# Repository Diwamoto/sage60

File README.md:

# Sage60

60% の分割キーボード。左右とも nRF52840（MX 版は XIAO nRF52840）で、左右間・PC とは BLE で無線接続する。右手の親指側にトラックボール（PMW3610）。
スイッチは MX / Kailh Choc v2（同じ PCB）と、東プレ（静電容量）版がある。

**[ギャラリーサイト](https://diwamoto.github.io/sage60/)**: 3D モデルと構造の解説（`case/site/`）

## ディレクトリ

| パス | 中身 |
| --- | --- |
| `pcb/mx/`, `pcb/ec/` | KiCad の基板・回路図（`pcb/README.md`） |
| `case/` | ケースを KiCad から作るスクリプト（Python + Fusion）。ガスケットマウント、磁石固定、MX とロープロファイル（`case/README.md`） |
| `case/trackball/` | トラックボールケースの改造スクリプトと取得手順（ケース本体は fork） |
| `firmware/zmk/` | ZMK の設定（shield `sage60` = MX、`sage60_ec` = 東プレ）。`build.sh` でローカルビルド、GitHub Actions でもビルド |
| `production/` | 発注・印刷に使う出力物 |
| `docs/` | 配列（`kle.json`）、配線図（`sage60_wiring.drawio`）、画像 |

`production/` の中身:

| パス | 用途 |
| --- | --- |
| `case_cnc/` | ケース上下の STEP（JLCCNC） |
| `case_print/` | ケース上下・MCU カバー・シムの 3MF / STL（3D プリント） |
| `plate/` | プレートの DXF（外形の元データ。ケース生成もここから読む）/ STEP（金属）、3MF（プリント） |
| `mcu_cover/` | MCU カバーの DXF（ウォルナット） |

## ファームウェア

ZMK。東プレ版は nRF52840 の ADC で静電容量を読んでキー入力を判定する（判定方法は[こちら](https://nogikes.booth.pm/items/2373281)、[こちら](https://booth.pm/ja/items/2232932)を参考）。

## ライセンス

MIT（`LICENSE`）。PMW3610 センサー基板とトラックボールケースは GPL-3.0 なので [Diwamoto/roBa の `sage60` ブランチ](https://github.com/Diwamoto/roBa/tree/sage60) に分けている。

## 参考
* zmk の設定: [tako-config](https://github.com/ssbb/tako-config)
* 基板: [tako](https://github.com/ssbb/tako)
* センサー基板・トラックボールケース: [roBa](https://github.com/kumamuk-git/roBa)（ケースの元は Keyball Trackball Case by kepeo）

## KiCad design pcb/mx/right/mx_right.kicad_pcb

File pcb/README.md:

# pcb

KiCad の元データ（`.kicad_pro` / `.kicad_pcb` / `.kicad_sch`）だけをコミットする。バックアップ・`.kicad_prl`・プラグイン設定・ガーバーなどの出力はローカルのみ（`.gitignore`）。発注に使うファイルは `production/`。JLCPCB 用ガーバーは `.kicad_pcb` を push すると Actions（`.github/workflows/gerber.yml`）が基板ごとの artifact `gerber-*` に出す。ダウンロードした zip をそのまま JLCPCB に上げられる。

| フォルダ | 中身 |
| --- | --- |
| `mx/left/` | MX 左のメイン基板（`mx.kicad_*`、XIAO nRF52840） |
| `mx/right/` | MX 右（トラックボール、PMW3610 センサー基板へ J1） |
| `ec/main/` | 東プレ（静電容量）左メイン |
| `ec/scan_module/` | 静電容量の読み取りモジュール |
| `modules/footprint/sage60.pretty/`、`modules/symbol/sage60.kicad_sym` | 自作部品（XIAO nRF52840 Plus）。`mx/right` と `ec/main` の `fp-lib-table` / `sym-lib-table` が読む |

PMW3610 センサー基板は GPL-3.0 なのでここには置かない。元データは [Diwamoto/roBa](https://github.com/Diwamoto/roBa/tree/sage60/pcb/pmw3610_breakout_for_roBa)（roBa のまま無改変）で、ガーバーは同じ Actions の `gerber-pmw3610_breakout` に出る。

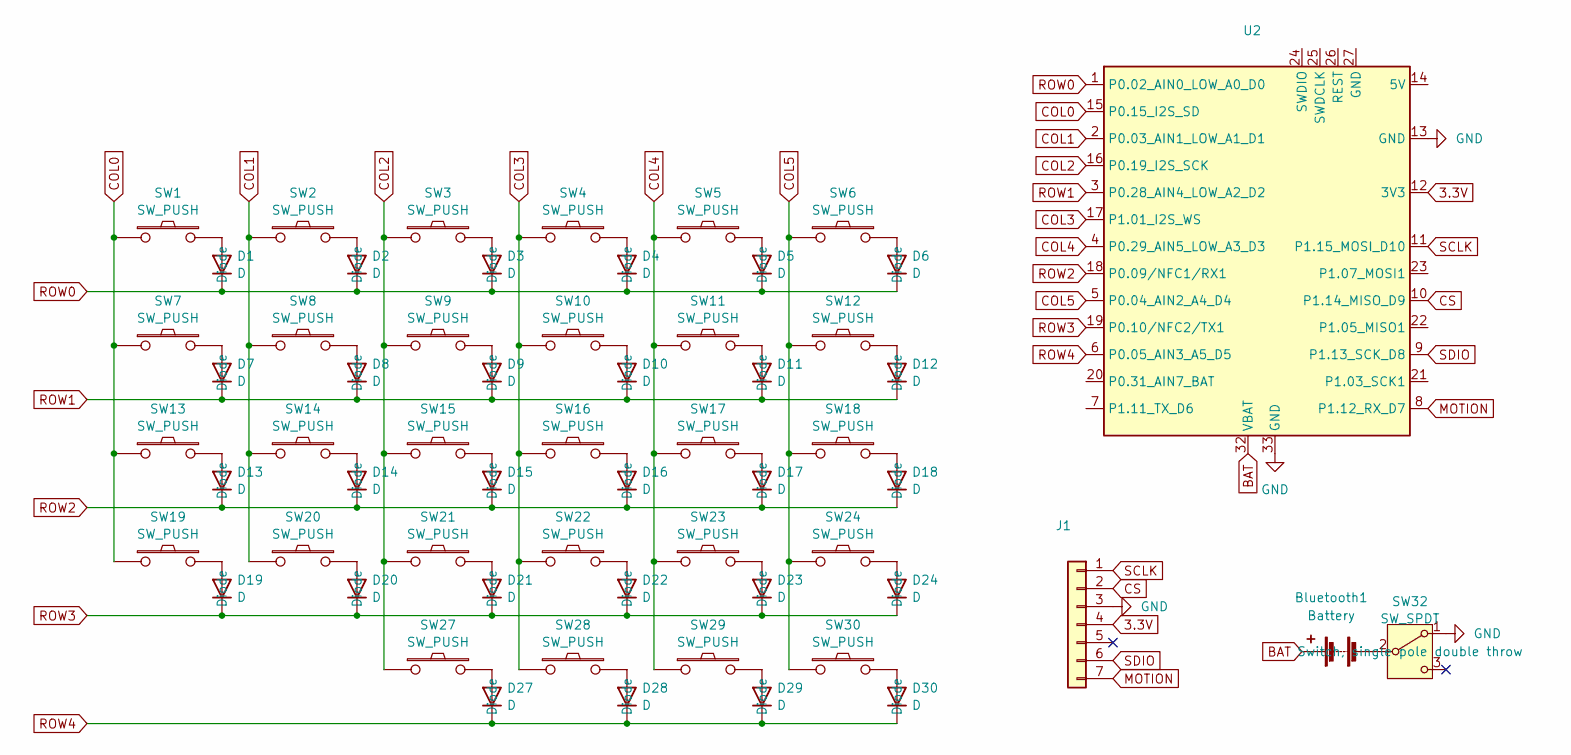
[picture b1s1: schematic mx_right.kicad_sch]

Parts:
Bluetooth1: Battery
D1, D2, D3, D4, D5, D6, D7, D8, D9, D10, D11, D12, D13, D14, D15, D16, D17, D18, D19, D20, D21, D22, D23, D24, D27, D28, D29, D30: D; D3_SMD_v2
J1: PinHeader_1x07_P2.54mm_Vertical
SW1, SW2, SW3, SW4, SW5, SW6, SW7, SW8, SW9, SW10, SW11, SW12, SW13, SW14, SW15, SW16, SW17, SW18, SW19, SW20, SW21, SW22, SW23, SW24, SW27, SW28, SW29, SW30: SW_PUSH; CherryMX_Choc_Hotswap_v2
SW32: SW_SPDT; PinHeader_1x03_P2.54mm_Vertical
U2: XIAO_nRF52840_Plus

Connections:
3.3V: J1.4, U2.12 (3V3)
BAT: Bluetooth1.1 (+), U2.32 (VBAT)
COL0: SW1.1, SW7.1, SW13.1, SW19.1, U2.15 (P0.15_I2S_SD)
COL1: SW2.1, SW8.1, SW14.1, SW20.1, U2.2 (P0.03_AIN1_LOW_A1_D1)
COL2: SW3.1, SW9.1, SW15.1, SW21.1, SW27.1, U2.16 (P0.19_I2S_SCK)
COL3: SW4.1, SW10.1, SW16.1, SW22.1, SW28.1, U2.17 (P1.01_I2S_WS)
COL4: SW5.1, SW11.1, SW17.1, SW23.1, SW29.1, U2.4 (P0.29_AIN5_LOW_A3_D3)
COL5: SW6.1, SW12.1, SW18.1, SW24.1, SW30.1, U2.5 (P0.04_AIN2_A4_D4)
CS: J1.2, U2.10 (P1.14_MISO_D9)
GND: J1.3, SW32.1 (A), U2.13 (GND), U2.33 (GND)
MOTION: J1.7, U2.8 (P1.12_RX_D7)
unnamed: Bluetooth1.2 (-), SW32.2 (B)
unnamed: D1.2 (A), SW1.2
unnamed: D2.2 (A), SW2.2
unnamed: D3.2 (A), SW3.2
unnamed: D4.2 (A), SW4.2
unnamed: D5.2 (A), SW5.2
unnamed: D6.2 (A), SW6.2
unnamed: D7.2 (A), SW7.2
unnamed: D8.2 (A), SW8.2
unnamed: D9.2 (A), SW9.2
unnamed: D10.2 (A), SW10.2
unnamed: D11.2 (A), SW11.2
unnamed: D12.2 (A), SW12.2
unnamed: D13.2 (A), SW13.2
unnamed: D14.2 (A), SW14.2
unnamed: D15.2 (A), SW15.2
unnamed: D16.2 (A), SW16.2
unnamed: D17.2 (A), SW17.2
unnamed: D18.2 (A), SW18.2
unnamed: D19.2 (A), SW19.2
unnamed: D20.2 (A), SW20.2
unnamed: D21.2 (A), SW21.2
unnamed: D22.2 (A), SW22.2
unnamed: D23.2 (A), SW23.2
unnamed: D24.2 (A), SW24.2
unnamed: D27.2 (A), SW27.2
unnamed: D28.2 (A), SW28.2
unnamed: D29.2 (A), SW29.2
unnamed: D30.2 (A), SW30.2
ROW0: D1.1 (K), D2.1 (K), D3.1 (K), D4.1 (K), D5.1 (K), D6.1 (K), U2.1 (P0.02_AIN0_LOW_A0_D0)
ROW1: D7.1 (K), D8.1 (K), D9.1 (K), D10.1 (K), D11.1 (K), D12.1 (K), U2.3 (P0.28_AIN4_LOW_A2_D2)
ROW2: D13.1 (K), D14.1 (K), D15.1 (K), D16.1 (K), D17.1 (K), D18.1 (K), U2.18 (P0.09/NFC1/RX1)
ROW3: D19.1 (K), D20.1 (K), D21.1 (K), D22.1 (K), D23.1 (K), D24.1 (K), U2.19 (P0.10/NFC2/TX1)
ROW4: D27.1 (K), D28.1 (K), D29.1 (K), D30.1 (K), U2.6 (P0.05_AIN3_A5_D5)
SCLK: J1.1, U2.11 (P1.15_MOSI_D10)
SDIO: J1.6, U2.9 (P1.13_SCK_D8)

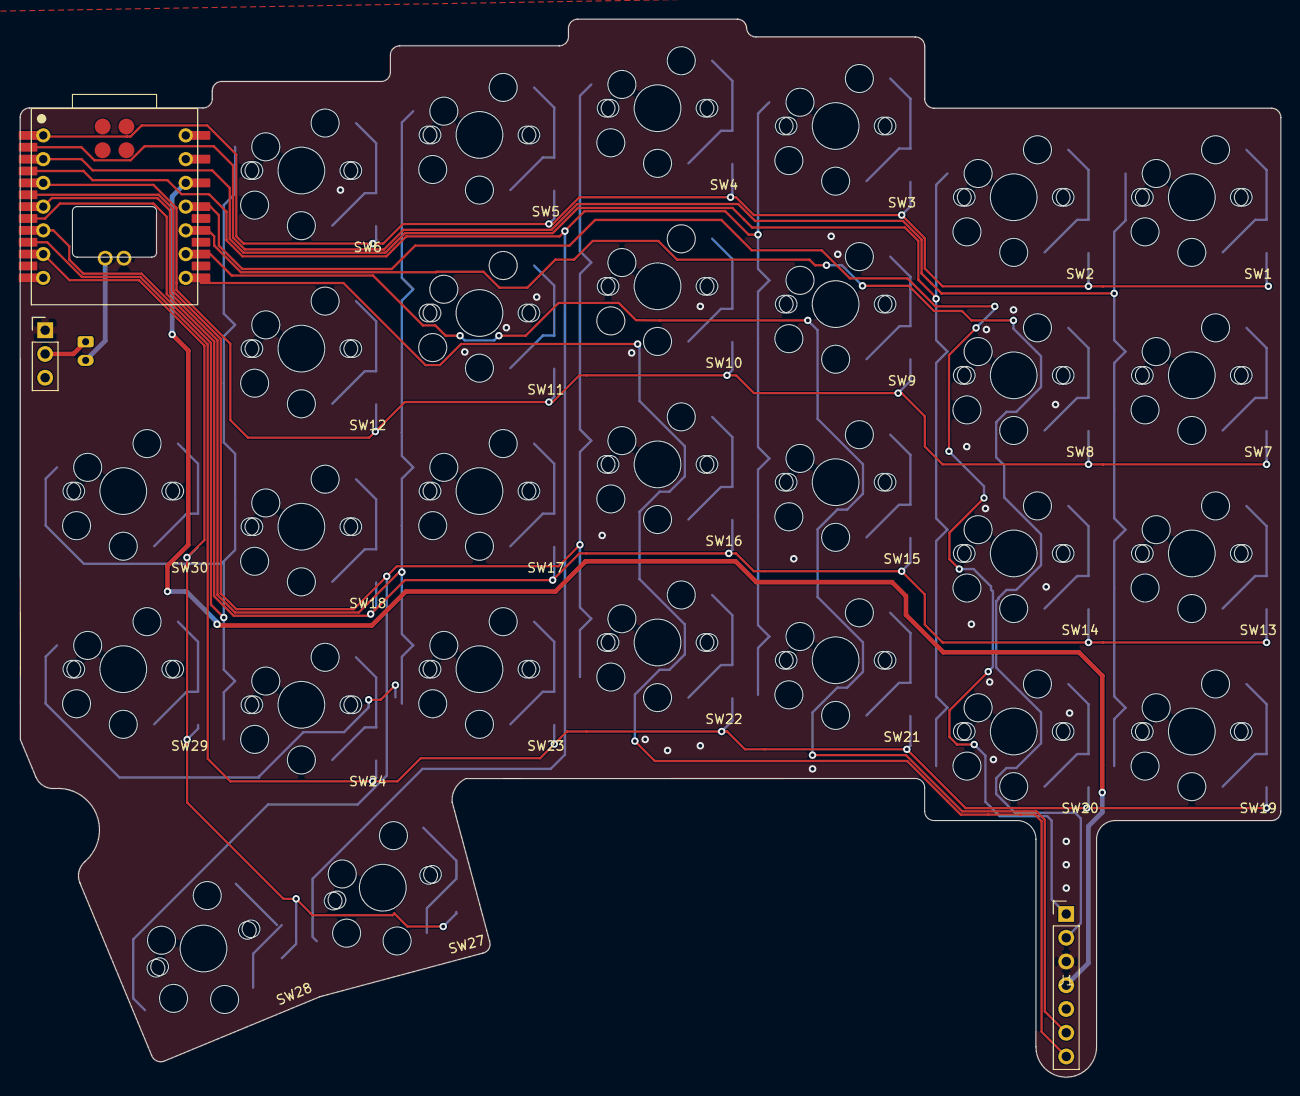
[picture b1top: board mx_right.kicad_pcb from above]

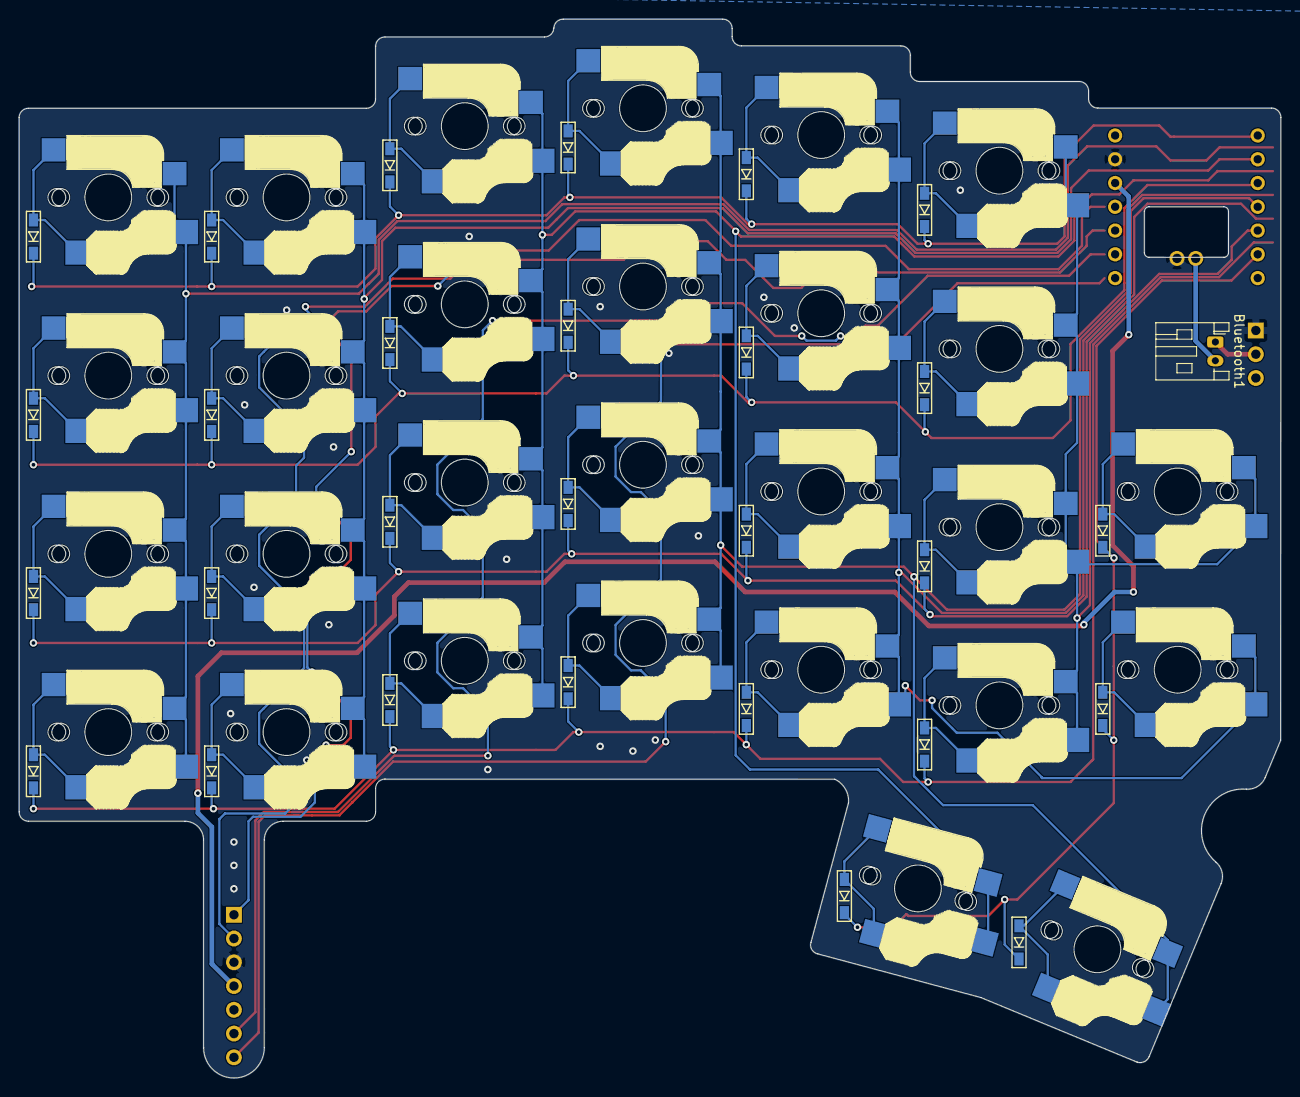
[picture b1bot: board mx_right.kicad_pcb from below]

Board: 2 copper layers, 134.9 x 113.2 mm, 60 parts (29 on the bottom side), 47 nets.

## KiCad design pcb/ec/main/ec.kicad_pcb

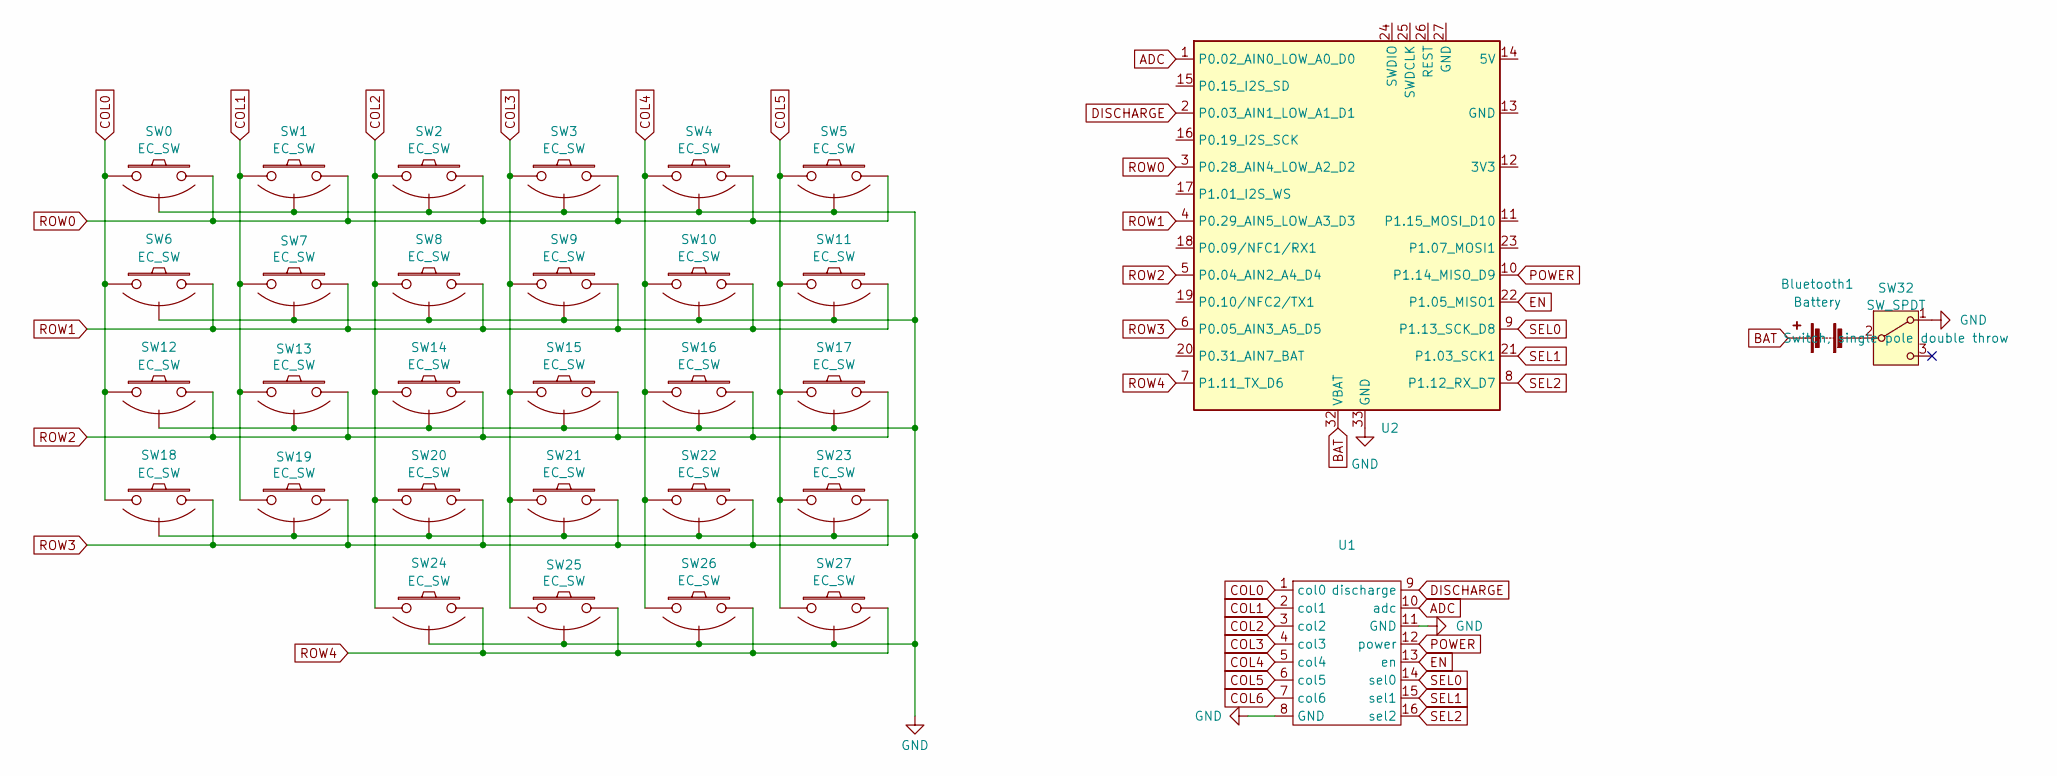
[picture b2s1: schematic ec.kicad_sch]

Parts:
Bluetooth1: Battery
SW0, SW1, SW2, SW3, SW4, SW5, SW6, SW7, SW8, SW9, SW10, SW11, SW12, SW13, SW14, SW15, SW16, SW17, SW18, SW19, SW20, SW21, SW22, SW23, SW24, SW25, SW26, SW27: EC_SW; ecs_pad_1U_no_ring
SW32: SW_SPDT; PinHeader_1x03_P2.54mm_Vertical
U1: ec_scan_module
U2: XIAO_nRF52840_Plus

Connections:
ADC: U1.10 (adc), U2.1 (P0.02_AIN0_LOW_A0_D0)
BAT: Bluetooth1.1 (+), U2.32 (VBAT)
COL0: SW0.1, SW6.1, SW12.1, SW18.1, U1.1 (col0)
COL1: SW1.1, SW7.1, SW13.1, SW19.1, U1.2 (col1)
COL2: SW2.1, SW8.1, SW14.1, SW20.1, SW24.1, U1.3 (col2)
COL3: SW3.1, SW9.1, SW15.1, SW21.1, SW25.1, U1.4 (col3)
COL4: SW4.1, SW10.1, SW16.1, SW22.1, SW26.1, U1.5 (col4)
COL5: SW5.1, SW11.1, SW17.1, SW23.1, SW27.1, U1.6 (col5)
COL6: U1.7 (col6)
DISCHARGE: U1.9 (discharge), U2.2 (P0.03_AIN1_LOW_A1_D1)
EN: U1.13 (en), U2.22 (P1.05_MISO1)
GND: SW0.3 (SG), SW1.3 (SG), SW2.3 (SG), SW3.3 (SG), SW4.3 (SG), SW5.3 (SG), SW6.3 (SG), SW7.3 (SG), SW8.3 (SG), SW9.3 (SG), SW10.3 (SG), SW11.3 (SG), SW12.3 (SG), SW13.3 (SG), SW14.3 (SG), SW15.3 (SG), SW16.3 (SG), SW17.3 (SG), SW18.3 (SG), SW19.3 (SG), SW20.3 (SG), SW21.3 (SG), SW22.3 (SG), SW23.3 (SG), SW24.3 (SG), SW25.3 (SG), SW26.3 (SG), SW27.3 (SG), SW32.1 (A), U1.8 (GND), U1.11 (GND), U2.33 (GND)
unnamed: Bluetooth1.2 (-), SW32.2 (B)
POWER: U1.12 (power), U2.10 (P1.14_MISO_D9)
ROW0: SW0.2, SW1.2, SW2.2, SW3.2, SW4.2, SW5.2, U2.3 (P0.28_AIN4_LOW_A2_D2)
ROW1: SW6.2, SW7.2, SW8.2, SW9.2, SW10.2, SW11.2, U2.4 (P0.29_AIN5_LOW_A3_D3)
ROW2: SW12.2, SW13.2, SW14.2, SW15.2, SW16.2, SW17.2, U2.5 (P0.04_AIN2_A4_D4)
ROW3: SW18.2, SW19.2, SW20.2, SW21.2, SW22.2, SW23.2, U2.6 (P0.05_AIN3_A5_D5)
ROW4: SW24.2, SW25.2, SW26.2, SW27.2, U2.7 (P1.11_TX_D6)
SEL0: U1.14 (sel0), U2.9 (P1.13_SCK_D8)
SEL1: U1.15 (sel1), U2.21 (P1.03_SCK1)
SEL2: U1.16 (sel2), U2.8 (P1.12_RX_D7)

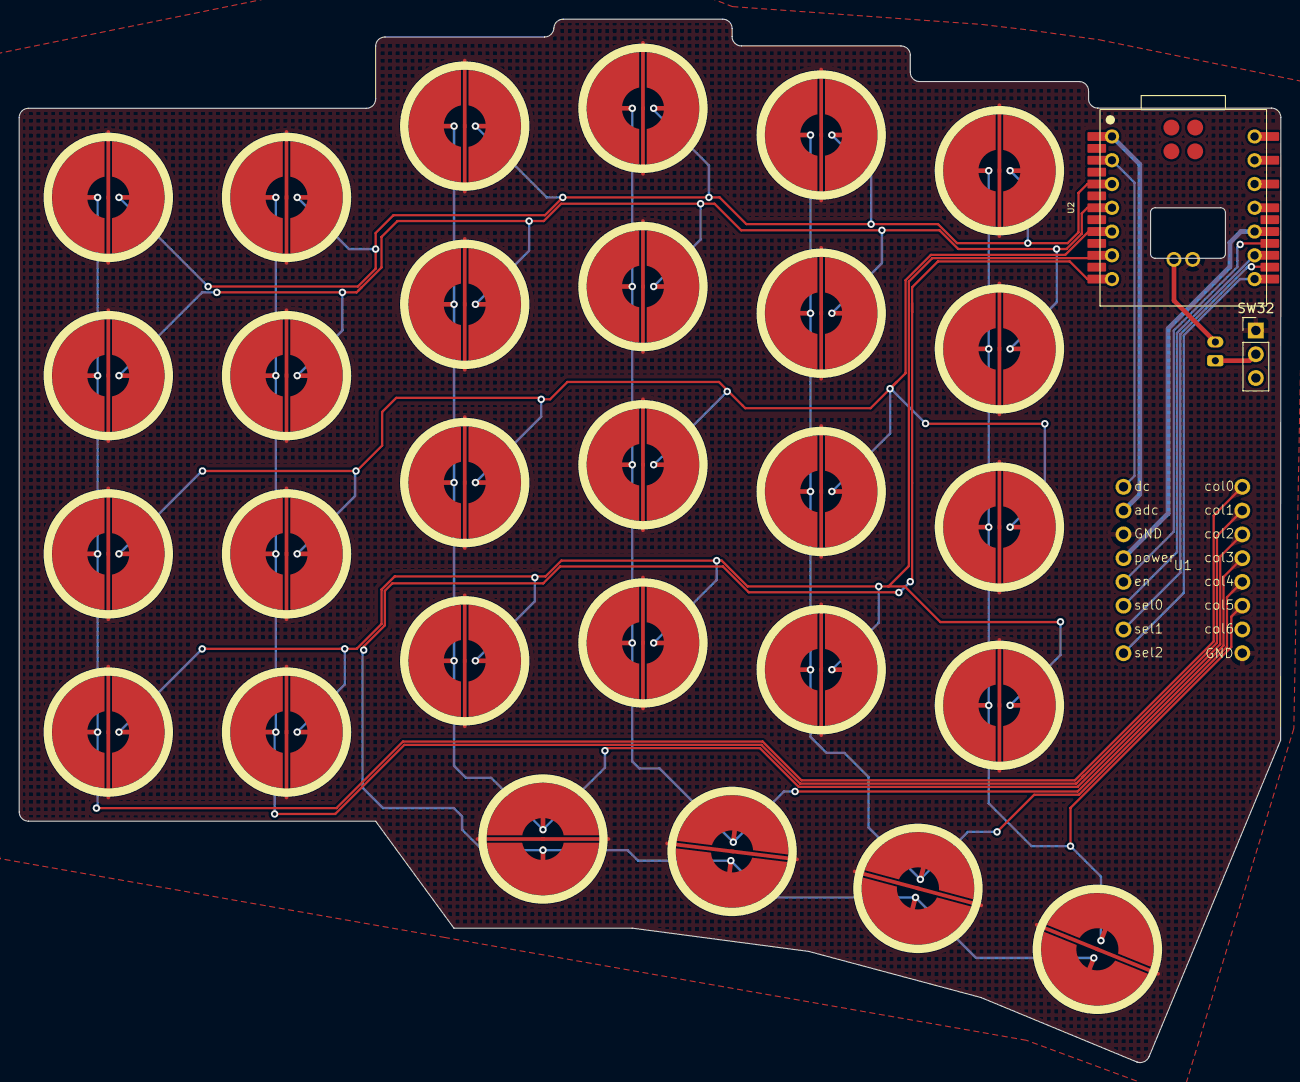
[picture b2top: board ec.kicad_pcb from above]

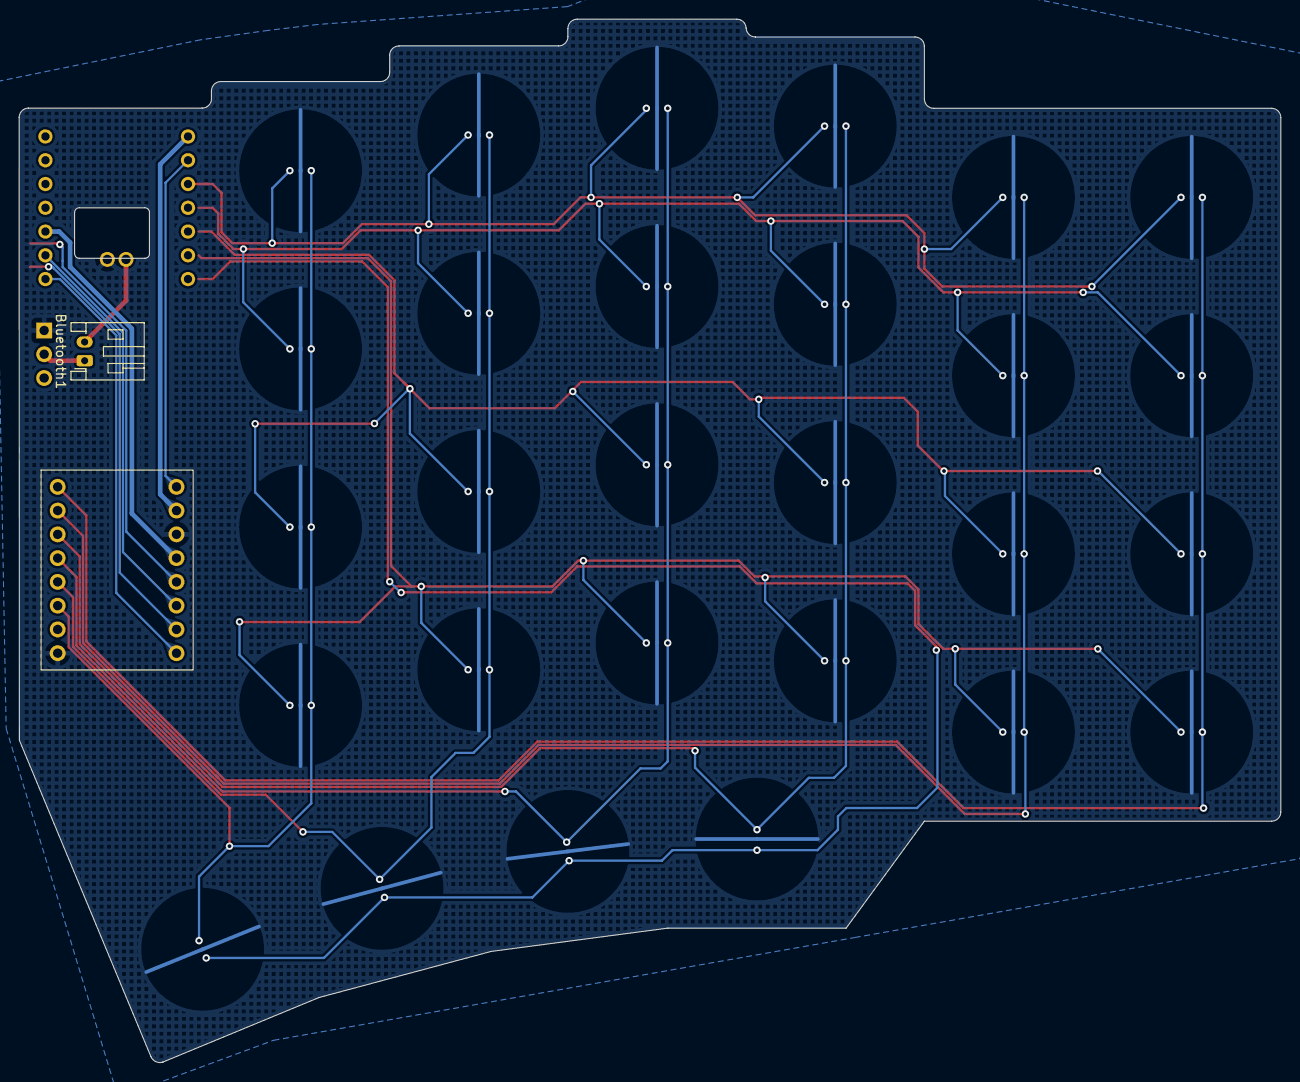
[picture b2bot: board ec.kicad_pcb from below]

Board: 2 copper layers, 134.9 x 111.5 mm, 32 parts (2 on the bottom side), 21 nets.

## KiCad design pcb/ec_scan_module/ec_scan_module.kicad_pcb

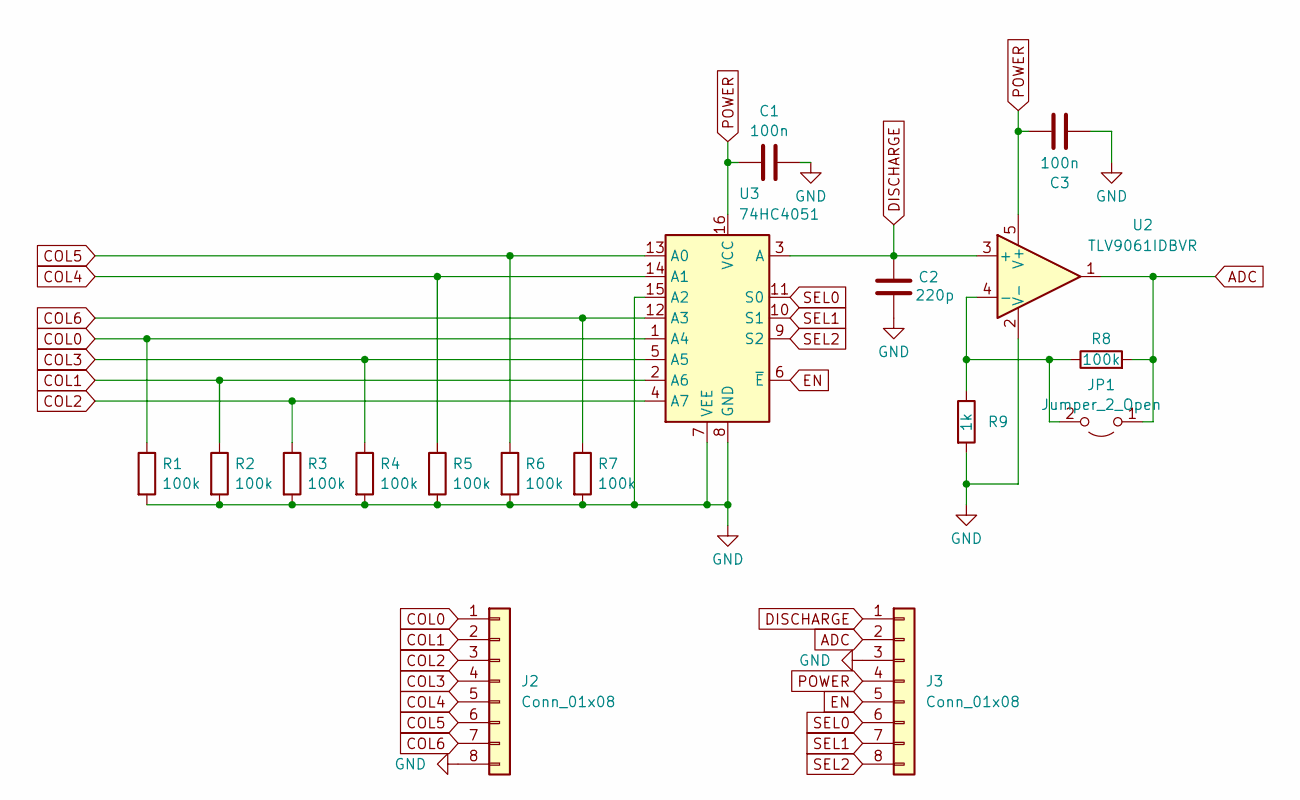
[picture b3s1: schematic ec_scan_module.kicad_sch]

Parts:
C1, C3: 100n; C_0402_1005Metric
C2: 220p; C_0402_1005Metric
J2, J3: Conn_01x08; PinHeader_1x08_P2.54mm_Vertical
JP1: Jumper_2_Open; R_0201_0603Metric_Pad0.64x0.40mm_HandSolder
R1, R2, R3, R4, R5, R6, R7, R8: 100k; R_0402_1005Metric
R9: 1k; R_0402_1005Metric
U2: TLV9061IDBVR; SOT-23-5
U3: 74HC4051; TSSOP-16_4.4x5mm_P0.65mm

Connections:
ADC: J3.2, JP1.1 (A), R8.2, U2.1
COL0: J2.1, R1.1, U3.1 (A4)
COL1: J2.2, R2.1, U3.2 (A6)
COL2: J2.3, R3.1, U3.4 (A7)
COL3: J2.4, R4.1, U3.5 (A5)
COL4: J2.5, R5.1, U3.14 (A1)
COL5: J2.6, R6.1, U3.13 (A0)
COL6: J2.7, R7.1, U3.12 (A3)
DISCHARGE: C2.2, J3.1, U2.3 (+), U3.3 (A)
EN: J3.5, U3.6 (~E)
GND: C1.2, C2.1, C3.1, J2.8, J3.3, R1.2, R2.2, R3.2, R4.2, R5.2, R6.2, R7.2, R9.2, U2.2 (V-), U3.7 (VEE), U3.8 (GND), U3.15 (A2)
unnamed: JP1.2 (B), R8.1, R9.1, U2.4 (-)
POWER: C1.1, C3.2, J3.4, U2.5 (V+), U3.16 (VCC)
SEL0: J3.6, U3.11 (S0)
SEL1: J3.7, U3.10 (S1)
SEL2: J3.8, U3.9 (S2)

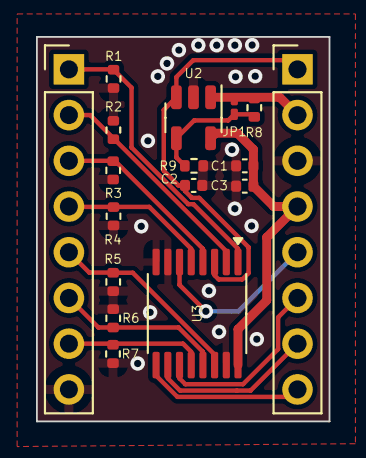
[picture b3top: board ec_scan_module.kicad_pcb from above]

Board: 2 copper layers, 16.3 x 21.4 mm, 17 parts (0 on the bottom side), 16 nets.

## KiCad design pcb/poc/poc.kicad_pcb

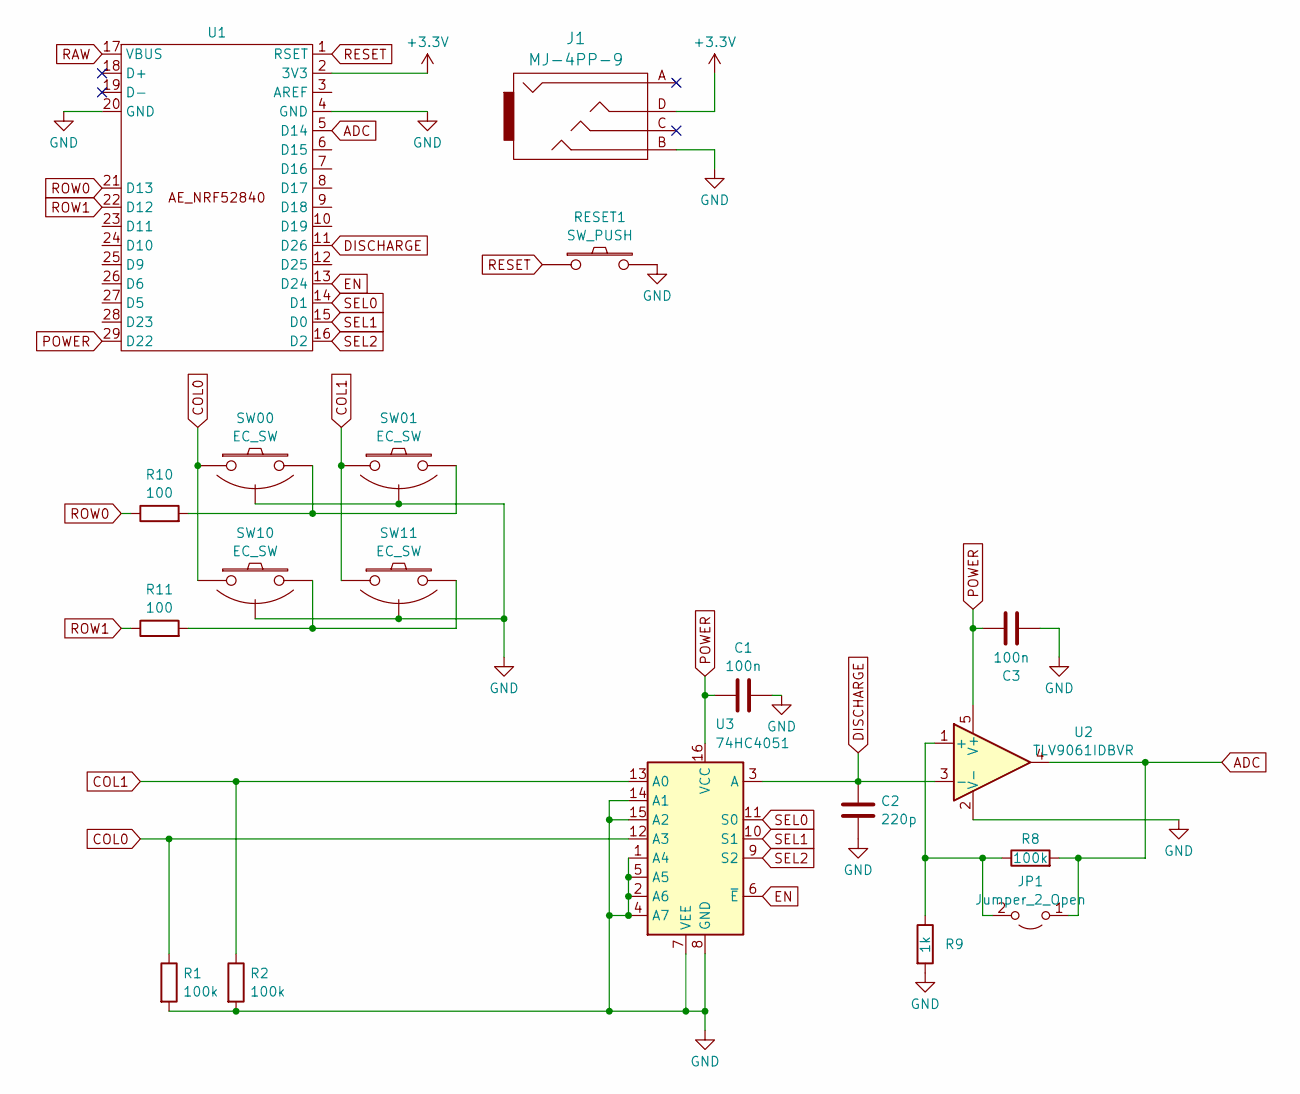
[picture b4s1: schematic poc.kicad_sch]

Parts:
C1, C3: 100n; C_0805_2012Metric_Pad1.18x1.45mm_HandSolder
C2: 220p; C_0805_2012Metric_Pad1.18x1.45mm_HandSolder
J1: MJ-4PP-9; MJ-4PP-9_1side
JP1: Jumper_2_Open; R_0805_2012Metric_Pad1.20x1.40mm_HandSolder
R1, R2, R8: 100k; R_0805_2012Metric_Pad1.20x1.40mm_HandSolder
R9: 1k; R_0805_2012Metric_Pad1.20x1.40mm_HandSolder
R10, R11: 100; R_0805_2012Metric_Pad1.20x1.40mm_HandSolder
RESET1: SW_PUSH; ResetSW_1side
SW00, SW01, SW10, SW11: EC_SW; ecs_pad_1U_no_ring_90deg
U1: ae_nrf52840
U2: TLV9061IDBVR; SOT-23-5
U3: 74HC4051; SOIC-16_3.9x9.9mm_P1.27mm

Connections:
+3.3V: J1.D, U1.2 (3V3)
ADC: JP1.1 (A), R8.2, U1.5 (D14), U2.4
COL0: R1.1, SW00.1, SW10.1, U3.12 (A3)
COL1: R2.1, SW01.1, SW11.1, U3.13 (A0)
DISCHARGE: C2.2, U1.11 (D26), U2.3 (-), U3.3 (A)
EN: U1.13 (D24), U3.6 (~E)
GND: C1.2, C2.1, C3.1, J1.B, R1.2, R2.2, R9.2, RESET1.2, SW00.3 (SG), SW01.3 (SG), SW10.3 (SG), SW11.3 (SG), U1.4 (GND), U1.20 (GND), U2.2 (V-), U3.1 (A4), U3.2 (A6), U3.4 (A7), U3.5 (A5), U3.7 (VEE), U3.8 (GND), U3.14 (A1), U3.15 (A2)
unnamed: JP1.2 (B), R8.1, R9.1, U2.1 (+)
unnamed: R10.2, SW00.2, SW01.2
unnamed: R11.2, SW10.2, SW11.2
POWER: C1.1, C3.2, U1.29 (D22), U2.5 (V+), U3.16 (VCC)
RAW: U1.17 (VBUS)
RESET: RESET1.1, U1.1 (RSET)
ROW0: R10.1, U1.21 (D13)
ROW1: R11.1, U1.22 (D12)
SEL0: U1.14 (D1), U3.11 (S0)
SEL1: U1.15 (D0), U3.10 (S1)
SEL2: U1.16 (D2), U3.9 (S2)

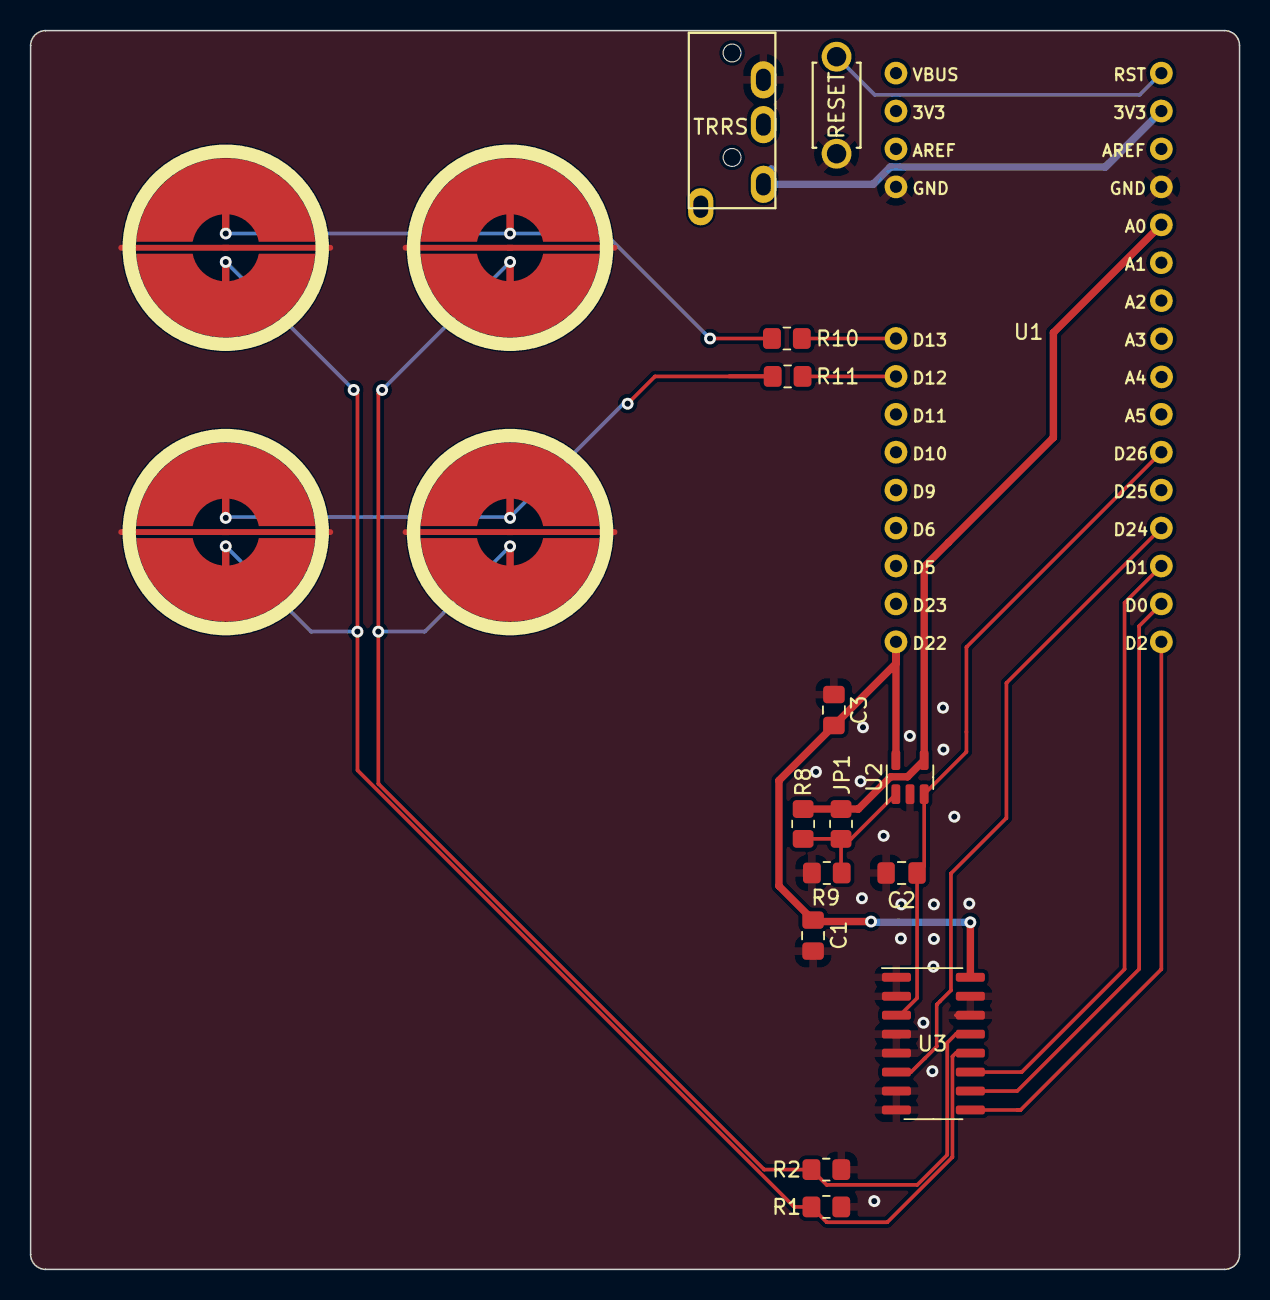
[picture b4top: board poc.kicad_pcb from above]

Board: 2 copper layers, 81.0 x 83.0 mm, 19 parts (0 on the bottom side), 17 nets.

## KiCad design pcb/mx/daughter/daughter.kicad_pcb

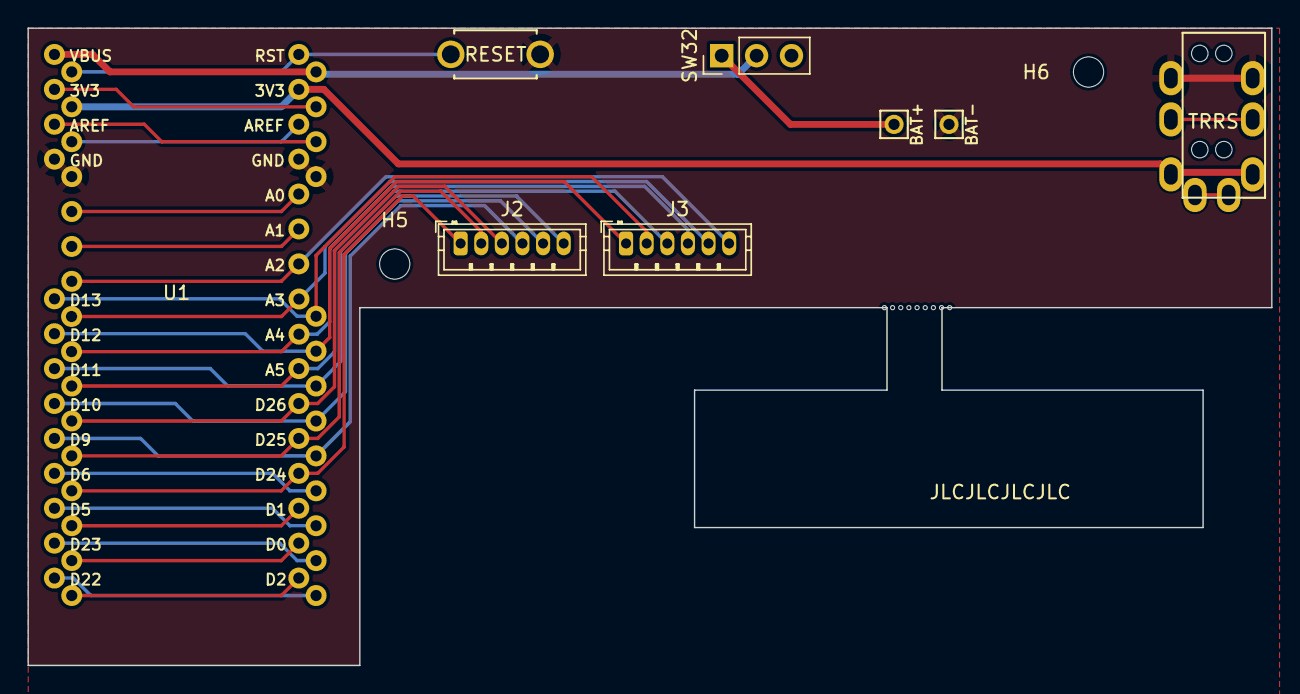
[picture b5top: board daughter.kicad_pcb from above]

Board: 2 copper layers, 90.5 x 46.4 mm, 10 parts (0 on the bottom side), 17 nets.

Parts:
BAT+: Conn_01x01_Pin; 1pin_conn
BAT-: Conn_01x01_Pin; 1pin_conn
H5, H6: MountingHole; MountingHole_2.2mm_M2
J1: MJ-4PP-9
J2, J3: Conn_01x06_Socket; JST_ZH_B6B-ZR_1x06_P1.50mm_Vertical
RESET1: SW_PUSH; ResetSW
SW32: SW_SPDT; PinHeader_1x03_P2.54mm_Vertical
U1: ae_nrf52840

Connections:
+3.3V: J1.D, U1.2 (3V3)
COL0: J2.1, U1.13 (D24)
COL1: J2.2, U1.12 (D25)
COL2: J2.3, U1.11 (D26)
COL3: J3.3, U1.10 (D19)
COL4: J3.4, U1.9 (D18)
COL5: J3.5, U1.8 (D17)
COL6: J3.6, U1.7 (D16)
GND: BAT-.1, J1.B, RESET1.2, U1.4 (GND), U1.20 (GND)
unnamed: BAT+.1, SW32.1 (A)
RAW: SW32.2 (B), U1.17 (VBUS)
RESET: RESET1.1, U1.1 (RSET)
ROW0: J3.2, U1.21 (D13)
ROW1: J3.1, U1.22 (D12)
ROW2: J2.6, U1.23 (D11)
ROW3: J2.5, U1.24 (D10)
ROW4: J2.4, U1.25 (D9)

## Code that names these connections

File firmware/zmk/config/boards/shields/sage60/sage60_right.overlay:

/*
 * Copyright (c) 2026 Diwamoto_
 * SPDX-License-Identifier: MIT
 *
 * Sage60 MX - right half with trackball (peripheral)
 * Source: pcb/mx/right/mx_right.kicad_pcb  (XIAO nRF52840 Plus = U2)
 *
 *  COL0 -> U2/15 P0.15           ROW0 -> U2/1  P0.02 (D0)
 *  COL1 -> U2/2  P0.03 (D1)      ROW1 -> U2/3  P0.28 (D2)
 *  COL2 -> U2/16 P0.19           ROW2 -> U2/18 P0.09 (NFC1)
 *  COL3 -> U2/17 P1.01           ROW3 -> U2/19 P0.10 (NFC2)
 *  COL4 -> U2/4  P0.29 (D3)      ROW4 -> U2/6  P0.05 (D5)
 *  COL5 -> U2/5  P0.04 (D4)
 *
 *  PMW3610 (J1): SCLK P1.15 (D10), SDIO P1.13 (D8), CS P1.14 (D9),
 *                MOTION P1.12 (D7)
 *
 * R4C0/R4C1 are not populated on this board (trackball sits there).
 * Columns are listed COL5..COL0 so that with col-offset = <6> the inner
 * column lands on matrix column 6 (keymap reads left-to-right).
 */

#include "sage60.dtsi"
#include <zephyr/dt-bindings/input/input-event-codes.h>

&default_transform {
    col-offset = <6>;
};

/* ROW2/ROW3 are on the NFC pads. */
&uicr {
    nfct-pins-as-gpios;
};

&kscan0 {
    row-gpios
        = <&gpio0  2 (GPIO_ACTIVE_HIGH | GPIO_PULL_DOWN)>   /* ROW0 P0.02 */
        , <&gpio0 28 (GPIO_ACTIVE_HIGH | GPIO_PULL_DOWN)>   /* ROW1 P0.28 */
        , <&gpio0  9 (GPIO_ACTIVE_HIGH | GPIO_PULL_DOWN)>   /* ROW2 P0.09 */
        , <&gpio0 10 (GPIO_ACTIVE_HIGH | GPIO_PULL_DOWN)>   /* ROW3 P0.10 */
        , <&gpio0  5 (GPIO_ACTIVE_HIGH | GPIO_PULL_DOWN)>   /* ROW4 P0.05 */
        ;

    col-gpios
        = <&gpio0  4 GPIO_ACTIVE_HIGH>   /* mcol0 = COL5 P0.04 */
        , <&gpio0 29 GPIO_ACTIVE_HIGH>   /* mcol1 = COL4 P0.29 */
        , <&gpio1  1 GPIO_ACTIVE_HIGH>   /* mcol2 = COL3 P1.01 */
        , <&gpio0 19 GPIO_ACTIVE_HIGH>   /* mcol3 = COL2 P0.19 */
        , <&gpio0  3 GPIO_ACTIVE_HIGH>   /* mcol4 = COL1 P0.03 */
        , <&gpio0 15 GPIO_ACTIVE_HIGH>   /* mcol5 = COL0 P0.15 */
        ;
};

/* PMW3610 is 3-wire SPI: MOSI and MISO share SDIO. */
&pinctrl {
    spi2_default: spi2_default {
        group1 {
            psels = <NRF_PSEL(SPIM_SCK, 1, 15)>,
                <NRF_PSEL(SPIM_MOSI, 1, 13)>,
                <NRF_PSEL(SPIM_MISO, 1, 13)>;
        };
    };

    spi2_sleep: spi2_sleep {
        group1 {
            psels = <NRF_PSEL(SPIM_SCK, 1, 15)>,
                <NRF_PSEL(SPIM_MOSI, 1, 13)>,
                <NRF_PSEL(SPIM_MISO, 1, 13)>;
            low-power-enable;
        };
    };
};

&spi2 {
    status = "okay";
    compatible = "nordic,nrf-spim";
    cs-gpios = <&gpio1 14 GPIO_ACTIVE_LOW>;

    trackball: trackball@0 {
        status = "okay";
        compatible = "pixart,pmw3610-alt";
        reg = <0>;
        spi-max-frequency = <1000000>;   /* sensor max 2 MHz; ~18 cm of trace to J1 */
        irq-gpios = <&gpio1 12 (GPIO_ACTIVE_LOW | GPIO_PULL_UP)>;
        cpi = <800>;
        /* Tune to the sensor's mounting orientation on the real board. */
        // swap-xy;
        // invert-x;
        invert-y;
        evt-type = <INPUT_EV_REL>;
        x-input-code = <INPUT_REL_X>;
        y-input-code = <INPUT_REL_Y>;
        force-awake;
    };
};

/* Raw motion goes to the left (central); rotation is applied there so it
 * can be tuned at runtime over BLE (see sage60_left.overlay). */
&trackball_split {
    device = <&trackball>;
};

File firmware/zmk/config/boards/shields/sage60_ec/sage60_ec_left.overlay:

/*
 * Copyright (c) 2026 Diwamoto_
 * SPDX-License-Identifier: MIT
 *
 * Sage60 EC - left half (central). Source: pcb/ec_main/ec.kicad_pcb (U2)
 *
 *  ADC  P0.02 (D0)   ROW0 P0.28 (D2)   SEL0 P1.13 (D8)    POWER P1.14 (D9)
 *  DISCHARGE P0.03   ROW1 P0.29 (D3)   SEL1 P1.03 (pad21) EN    P1.05 (pad22)
 *                    ROW2 P0.04 (D4)   SEL2 P1.12 (D7)
 *                    ROW3 P0.05 (D5)
 *                    ROW4 P1.11 (D6)
 */

#include "sage60_ec.dtsi"

&mux {
    select-gpios
        = <&gpio1 13 GPIO_ACTIVE_HIGH>   /* SEL0 */
        , <&gpio1  3 GPIO_ACTIVE_HIGH>   /* SEL1 */
        , <&gpio1 12 GPIO_ACTIVE_HIGH>   /* SEL2 */
        ;
    en-gpios = <&gpio1 5 GPIO_ACTIVE_LOW>;
};

&matrix {
    strobe-gpios
        = <&gpio0 28 GPIO_ACTIVE_HIGH>   /* ROW0 */
        , <&gpio0 29 GPIO_ACTIVE_HIGH>   /* ROW1 */
        , <&gpio0  4 GPIO_ACTIVE_HIGH>   /* ROW2 */
        , <&gpio0  5 GPIO_ACTIVE_HIGH>   /* ROW3 */
        , <&gpio1 11 GPIO_ACTIVE_HIGH>   /* ROW4 */
        ;
    input-gpios
        = <&mux 4 0>   /* COL0 */
        , <&mux 6 0>   /* COL1 */
        , <&mux 7 0>   /* COL2 */
        , <&mux 5 0>   /* COL3 */
        , <&mux 1 0>   /* COL4 */
        , <&mux 0 0>   /* COL5 */
        ;
    /* ROW4 has no COL0/COL1 */
    strobe-input-masks = <0 0 0 0 (BIT(0) | BIT(1))>;
    drain-gpios = <&gpio0 3 GPIO_ACTIVE_HIGH>;
    power-gpios = <&gpio1 14 GPIO_ACTIVE_HIGH>;
};

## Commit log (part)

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2023-09-30 Add keyboard layout editor json
2024-01-14 Fix keyboard layout editorで読み込めるようにjsonを調整
2024-01-14 Add README.md
2024-01-14 Add kle image
2024-01-20 Add main
2024-01-20 Add poc
2024-01-20 Add readme
2024-01-23 Fix pocの設定を変更
2024-01-23 Add mx版の基板
2024-01-23 Add mxのdaughter
2024-01-23 Fix フォルダ変更
2024-01-23 Fix 穴の位置を微調整
2024-01-23 Add プレート
2024-01-25 Fix 微調整
2024-02-22 release: sage60 v0.0.1
2024-02-22 add: auto release github actions
2024-02-22 chore: unnecessary setting
2024-02-22 chore: github actions settings
2024-02-28 feat: fix kle.json for vial
2024-04-09 chore(master): release 1.1.0
2024-09-15 feat: add ec_saan_module
